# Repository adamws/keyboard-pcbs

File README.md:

# keyboard-pcbs

Collection of generated keyboard PCBs based on [via](https://github.com/the-via/keyboards.git) layouts.

:link: Visit [https://adamws.github.io/keyboard-pcbs](https://adamws.github.io/keyboard-pcbs) to view results.

> [!WARNING]
> This is a showcase/benchmark of [kicad-kbplacer](https://github.com/adamws/kicad-kbplacer) plugin.
> All of the KiCad files are automatically generated and *may* contain errors.
> These *are not* production ready PCBs.

## How to run

The procedure of generating `keyboard-pcbs` website is split into two stages
which can be repeated locally using builder docker image.

- Download all layouts from [via](https://github.com/the-via/keyboards.git)
repository and generate KiCad schematic and PCB file for each one.

  ```bash
  $ docker run --rm -v $(pwd):/work \
      ghcr.io/adamws/keyboard-pcbs-maker:latest python via_layouts_to_boards.py generate
  ```

- Collect results from first stage and create static website to be deployed

  ```bash
  $ docker run --rm -v $(pwd):/work \
      ghcr.io/adamws/keyboard-pcbs-maker:latest python via_layouts_to_boards.py collect
  ```

> [!WARNING]
> This takes long time and is resource consuming.
> It runs on schedule using [Github Actions](https://github.com/adamws/keyboard-pcbs/actions/workflows/main.yml).

To see results, go to output directory and start http server with python:

```bash
$ cd gh-pages
$ python -m http.server
Serving HTTP on 0.0.0.0 port 8000 (http://0.0.0.0:8000/) ...
```

### Run for single layout

If you want to run this for single layout file, call `kbplacer-generate.sh` directly.
For example, navigate to directory with `.json` layout and run:

```bash
$ cd src/gh60/satan
$ ls
satan.json
$ docker run --rm -v $(pwd):/work \
    ghcr.io/adamws/keyboard-pcbs-maker:latest kbplacer-generate.sh /work satan
```

Note that second argument passed to `kbplacer-generate.sh` does not contain file extension.

When container finish, current directory should contain following files:

```bash
$ ls
satan.json      satan-layout.svg  satan-schematic.svg
satan-kle.json  satan-render.svg  satan.zip
$ unzip satan.zip
Archive:  satan.zip
  inflating: satan.kicad_pro
  inflating: satan.kicad_sch
  inflating: satan.kicad_pcb
  inflating: satan.net
```

| satan-layout.svg                      |
| :-:                                   |
|  |

| satan-layout.svg                                                                                                   | satan-render.svg                                                                                                |
| :-:                                                                                                                | :-:                                                                                                             |
|                                                                         |                                                                        |
| [open in new window](https://raw.githubusercontent.com/adamws/keyboard-pcbs/master/resources/satan-schematic.svg)  | [open in new window](https://raw.githubusercontent.com/adamws/keyboard-pcbs/master/resources/satan-render.svg)  |

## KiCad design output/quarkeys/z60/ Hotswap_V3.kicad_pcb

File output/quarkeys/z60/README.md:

## quarkeys/z60/Hotswap-V2

[layout](Hotswap-V2-kle.json) - [PCB](Hotswap-V2.kicad_pcb)

{:loading="lazy"}

[Open in keyboard-layout-editor](http://www.keyboard-layout-editor.com/##@@_x:1&c=#aaaaaa;&=0,0&_c=#cccccc;&=0,1&=0,2&=0,3&=0,4&=0,5&=0,6&=0,7&=0,8&=0,9&=0,10&=0,11&=0,12&_w:2;&=0,14;&@_x:1&w:1.5;&=1,0&=1,2&=1,3&=1,4&=1,5&=1,6&=1,7&=1,8&=1,9&=1,10&=1,11&=1,12&=1,13&_w:1.5;&=1,14;&@_x:1&w:1.75;&=2,0&=2,2&=2,3&=2,4&=2,5&=2,6&=2,7&=2,8&=2,9&=2,10&=2,11&=2,12&_w:2.25;&=2,13;&@_x:1&w:2.25;&=3,1&=3,2&=3,3&=3,4&=3,5&=3,6&=3,7&=3,8&=3,9&=3,10&=3,11&_w:1.75;&=3,13&=3,14;&@_x:1&w:1.5;&=4,0&=4,2&_w:1.5;&=4,3&_w:7;&=4,7&_w:1.5;&=4,11&=4,13&_w:1.5;&=4,14)

{:loading="lazy"}

## quarkeys/z60/Solder-V2

[layout](Solder-V2-kle.json) - [PCB](Solder-V2.kicad_pcb)

{:loading="lazy"}

[Open in keyboard-layout-editor](http://www.keyboard-layout-editor.com/##@@_x:2.5&c=#777777;&=0,0&_c=#cccccc;&=0,1&=0,2&=0,3&=0,4&=0,5&=0,6&=0,7&=0,8&=0,9&=0,10&=0,11&=0,12&_c=#aaaaaa&w:2;&=0,13%0A%0A%0A0,0;&@_x:2.5&w:1.5;&=1,1&_c=#cccccc;&=1,2&=1,3&=1,4&=1,5&=1,6&=1,7&=1,8&=1,9&=1,10&=1,11&=1,12&=1,13&_w:1.5;&=1,14%0A%0A%0A1,0;&@_x:2.5&c=#aaaaaa&w:1.75;&=2,1&_c=#cccccc;&=2,2&=2,3&=2,4&=2,5&=2,6&=2,7&=2,8&=2,9&=2,10&=2,11&=2,12&_c=#777777&w:2.25;&=2,14%0A%0A%0A1,0;&@_x:2.5&c=#aaaaaa&w:2.25;&=3,0%0A%0A%0A2,0&_c=#cccccc;&=3,2&=3,3&=3,4&=3,5&=3,6&=3,7&=3,8&=3,9&=3,10&=3,11&_c=#aaaaaa&w:2.75;&=3,12%0A%0A%0A3,0;&@_x:2.5&w:1.25;&=4,0%0A%0A%0A4,0&_w:1.25;&=4,1%0A%0A%0A4,0&_w:1.25;&=4,3%0A%0A%0A4,0&_c=#cccccc&w:6.25;&=4,6%0A%0A%0A4,0&_c=#aaaaaa&w:1.25;&=4,10%0A%0A%0A4,0&_w:1.25;&=4,11%0A%0A%0A4,0&_w:1.25;&=4,12%0A%0A%0A4,0&_w:1.25;&=4,13%0A%0A%0A4,0;&@_x:18.0&y:-5&c=#cccccc;&=0,13%0A%0A%0A0,1&=0,14%0A%0A%0A0,1;&@_x:18.75&c=#777777&w:1.25&h:2&w2:1.5&h2:1&x2:-0.25;&=2,14%0A%0A%0A1,1;&@_x:17.75&c=#cccccc;&=2,13%0A%0A%0A1,1;&@_c=#aaaaaa&w:1.25;&=3,0%0A%0A%0A2,1&=3,1%0A%0A%0A2,1&_x:15.5&w:1.75;&=3,12%0A%0A%0A3,1&=3,13%0A%0A%0A3,1;&@_x:2.5&y:1.5&w:1.5;&=4,0%0A%0A%0A4,1&=4,1%0A%0A%0A4,1&_w:1.5;&=4,3%0A%0A%0A4,1&_c=#cccccc&w:7;&=4,6%0A%0A%0A4,1&_c=#aaaaaa&w:1.5;&=4,11%0A%0A%0A4,1&=4,12%0A%0A%0A4,1&_w:1.5;&=4,13%0A%0A%0A4,1;&@_x:2.5&w:1.5&d:true;&=4,0%0A%0A%0A4,2&=4,1%0A%0A%0A4,2&_w:1.5;&=4,3%0A%0A%0A4,2&_c=#cccccc&w:7;&=4,6%0A%0A%0A4,2&_c=#aaaaaa&w:1.5;&=4,11%0A%0A%0A4,2&=4,12%0A%0A%0A4,2&_w:1.5&d:true;&=4,13%0A%0A%0A4,2;&@_x:2.5&w:1.5;&=4,0%0A%0A%0A4,3&_d:true;&=4,1%0A%0A%0A4,3&_w:1.5;&=4,3%0A%0A%0A4,3&_c=#cccccc&w:7;&=4,6%0A%0A%0A4,3&_c=#aaaaaa&w:1.5;&=4,11%0A%0A%0A4,3&_d:true;&=4,12%0A%0A%0A4,3&_w:1.5;&=4,13%0A%0A%0A4,3)

{:loading="lazy"}

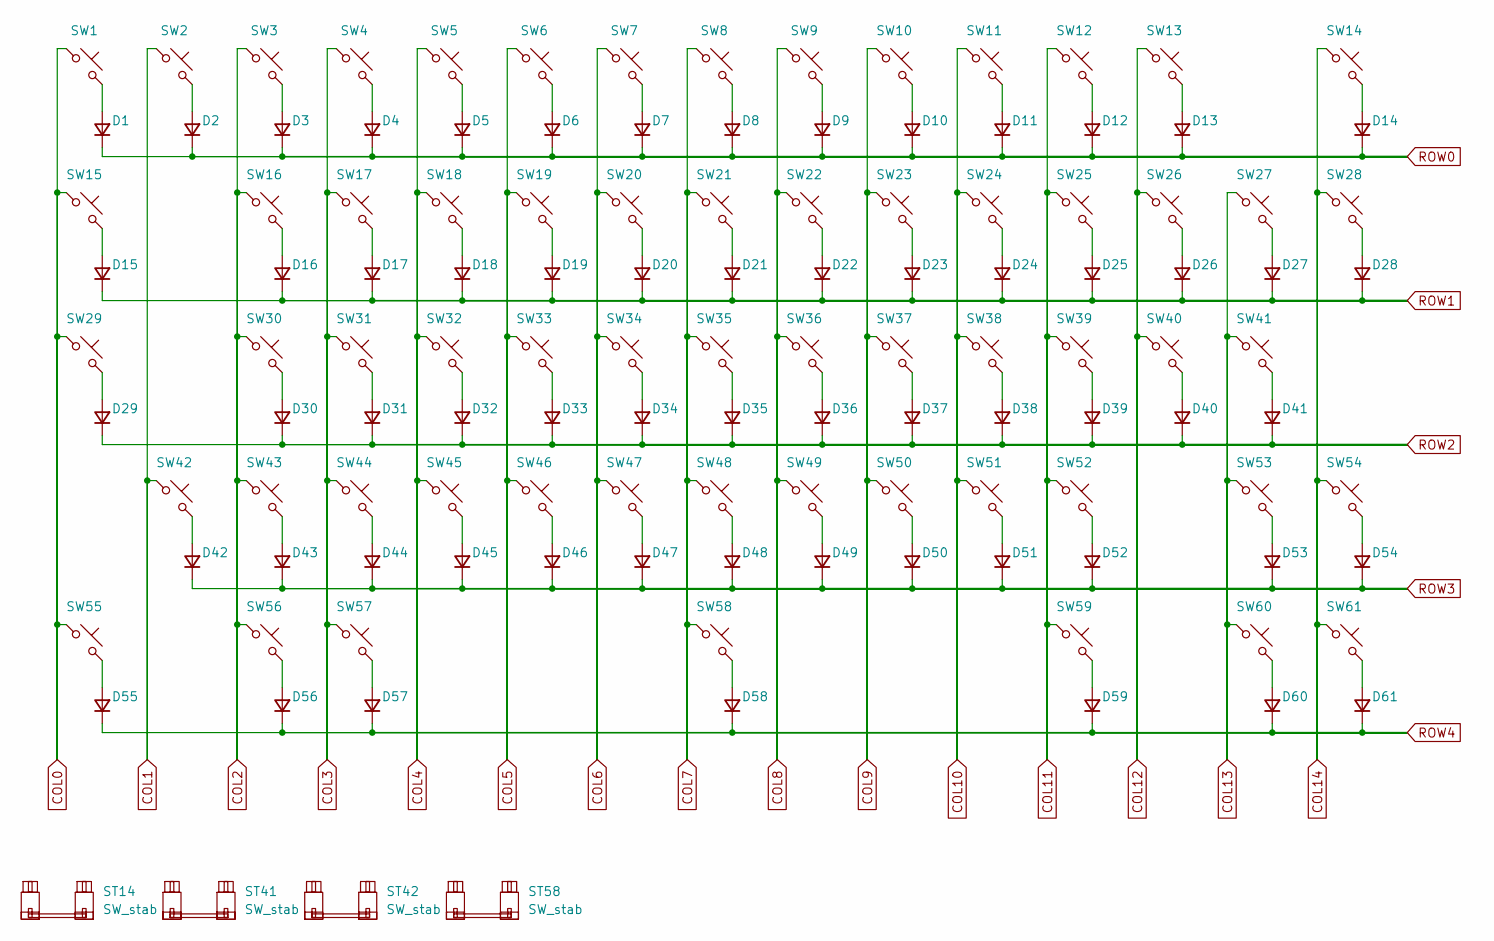
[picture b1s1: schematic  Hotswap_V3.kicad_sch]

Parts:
D1, D2, D3, D4, D5, D6, D7, D8, D9, D10, D11, D12, D13, D14, D15, D16, D17, D18, D19, D20, D21, D22, D23, D24, D25, D26, D27, D28, D29, D30, D31, D32, D33, D34, D35, D36, D37, D38, D39, D40, D41, D42, D43, D44, D45, D46, D47, D48, D49, D50, D51, D52, D53, D54, D55, D56, D57, D58, D59, D60, D61: D; D_SOD-123F
ST14, ST41, ST42: SW_stab; Stabilizer_Cherry_MX_2.00u
ST58: SW_stab; Stabilizer_Cherry_MX_7.00u
SW1, SW2, SW3, SW4, SW5, SW6, SW7, SW8, SW9, SW10, SW11, SW12, SW13, SW16, SW17, SW18, SW19, SW20, SW21, SW22, SW23, SW24, SW25, SW26, SW27, SW30, SW31, SW32, SW33, SW34, SW35, SW36, SW37, SW38, SW39, SW40, SW43, SW44, SW45, SW46, SW47, SW48, SW49, SW50, SW51, SW52, SW54, SW56, SW60: SW_Push; SW_Cherry_MX_PCB_1.00u
SW14: SW_Push; SW_Cherry_MX_PCB_2.00u
SW15, SW28, SW55, SW57, SW59, SW61: SW_Push; SW_Cherry_MX_PCB_1.50u
SW29, SW53: SW_Push; SW_Cherry_MX_PCB_1.75u
SW41, SW42: SW_Push; SW_Cherry_MX_PCB_2.25u
SW58: SW_Push; SW_Cherry_MX_PCB_7.00u

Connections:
COL0: SW1.1, SW15.1, SW29.1, SW55.1
COL1: SW2.1, SW42.1
COL2: SW3.1, SW16.1, SW30.1, SW43.1, SW56.1
COL3: SW4.1, SW17.1, SW31.1, SW44.1, SW57.1
COL4: SW5.1, SW18.1, SW32.1, SW45.1
COL5: SW6.1, SW19.1, SW33.1, SW46.1
COL6: SW7.1, SW20.1, SW34.1, SW47.1
COL7: SW8.1, SW21.1, SW35.1, SW48.1, SW58.1
COL8: SW9.1, SW22.1, SW36.1, SW49.1
COL9: SW10.1, SW23.1, SW37.1, SW50.1
COL10: SW11.1, SW24.1, SW38.1, SW51.1
COL11: SW12.1, SW25.1, SW39.1, SW52.1, SW59.1
COL12: SW13.1, SW26.1, SW40.1
COL13: SW27.1, SW41.1, SW53.1, SW60.1
COL14: SW14.1, SW28.1, SW54.1, SW61.1
unnamed: D1.2 (A), SW1.2
unnamed: D2.2 (A), SW2.2
unnamed: D3.2 (A), SW3.2
unnamed: D4.2 (A), SW4.2
unnamed: D5.2 (A), SW5.2
unnamed: D6.2 (A), SW6.2
unnamed: D7.2 (A), SW7.2
unnamed: D8.2 (A), SW8.2
unnamed: D9.2 (A), SW9.2
unnamed: D10.2 (A), SW10.2
unnamed: D11.2 (A), SW11.2
unnamed: D12.2 (A), SW12.2
unnamed: D13.2 (A), SW13.2
unnamed: D14.2 (A), SW14.2
unnamed: D15.2 (A), SW15.2
unnamed: D16.2 (A), SW16.2
unnamed: D17.2 (A), SW17.2
unnamed: D18.2 (A), SW18.2
unnamed: D19.2 (A), SW19.2
unnamed: D20.2 (A), SW20.2
unnamed: D21.2 (A), SW21.2
unnamed: D22.2 (A), SW22.2
unnamed: D23.2 (A), SW23.2
unnamed: D24.2 (A), SW24.2
unnamed: D25.2 (A), SW25.2
unnamed: D26.2 (A), SW26.2
unnamed: D27.2 (A), SW27.2
unnamed: D28.2 (A), SW28.2
unnamed: D29.2 (A), SW29.2
unnamed: D30.2 (A), SW30.2
unnamed: D31.2 (A), SW31.2
unnamed: D32.2 (A), SW32.2
unnamed: D33.2 (A), SW33.2
unnamed: D34.2 (A), SW34.2
unnamed: D35.2 (A), SW35.2
unnamed: D36.2 (A), SW36.2
unnamed: D37.2 (A), SW37.2
unnamed: D38.2 (A), SW38.2
unnamed: D39.2 (A), SW39.2
unnamed: D40.2 (A), SW40.2
unnamed: D41.2 (A), SW41.2
unnamed: D42.2 (A), SW42.2
unnamed: D43.2 (A), SW43.2
unnamed: D44.2 (A), SW44.2
unnamed: D45.2 (A), SW45.2
unnamed: D46.2 (A), SW46.2
unnamed: D47.2 (A), SW47.2
unnamed: D48.2 (A), SW48.2
unnamed: D49.2 (A), SW49.2
unnamed: D50.2 (A), SW50.2
unnamed: D51.2 (A), SW51.2
unnamed: D52.2 (A), SW52.2
unnamed: D53.2 (A), SW53.2
unnamed: D54.2 (A), SW54.2
unnamed: D55.2 (A), SW55.2
unnamed: D56.2 (A), SW56.2
unnamed: D57.2 (A), SW57.2
unnamed: D58.2 (A), SW58.2
unnamed: D59.2 (A), SW59.2
unnamed: D60.2 (A), SW60.2
unnamed: D61.2 (A), SW61.2
ROW0: D1.1 (K), D2.1 (K), D3.1 (K), D4.1 (K), D5.1 (K), D6.1 (K), D7.1 (K), D8.1 (K), D9.1 (K), D10.1 (K), D11.1 (K), D12.1 (K), D13.1 (K), D14.1 (K)
ROW1: D15.1 (K), D16.1 (K), D17.1 (K), D18.1 (K), D19.1 (K), D20.1 (K), D21.1 (K), D22.1 (K), D23.1 (K), D24.1 (K), D25.1 (K), D26.1 (K), D27.1 (K), D28.1 (K)
ROW2: D29.1 (K), D30.1 (K), D31.1 (K), D32.1 (K), D33.1 (K), D34.1 (K), D35.1 (K), D36.1 (K), D37.1 (K), D38.1 (K), D39.1 (K), D40.1 (K), D41.1 (K)
ROW3: D42.1 (K), D43.1 (K), D44.1 (K), D45.1 (K), D46.1 (K), D47.1 (K), D48.1 (K), D49.1 (K), D50.1 (K), D51.1 (K), D52.1 (K), D53.1 (K), D54.1 (K)
ROW4: D55.1 (K), D56.1 (K), D57.1 (K), D58.1 (K), D59.1 (K), D60.1 (K), D61.1 (K)

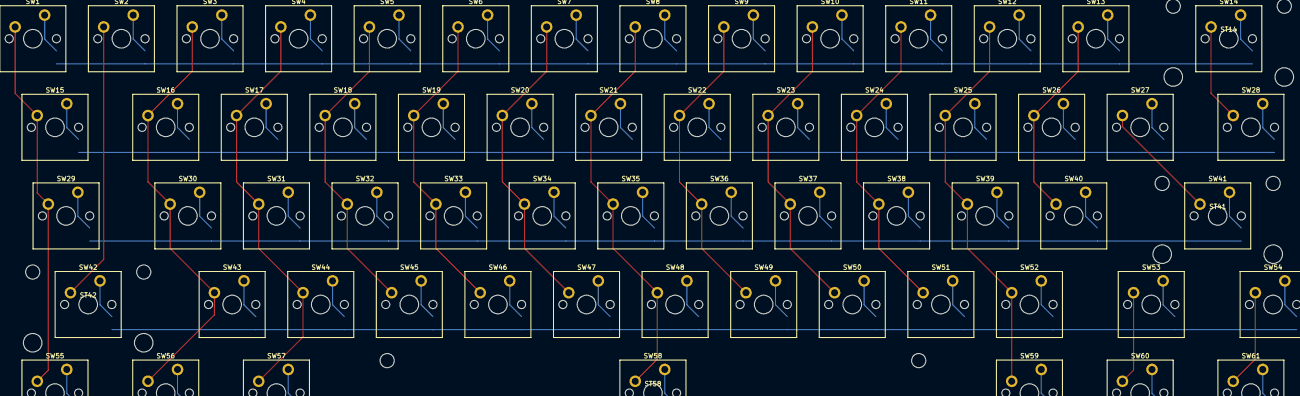
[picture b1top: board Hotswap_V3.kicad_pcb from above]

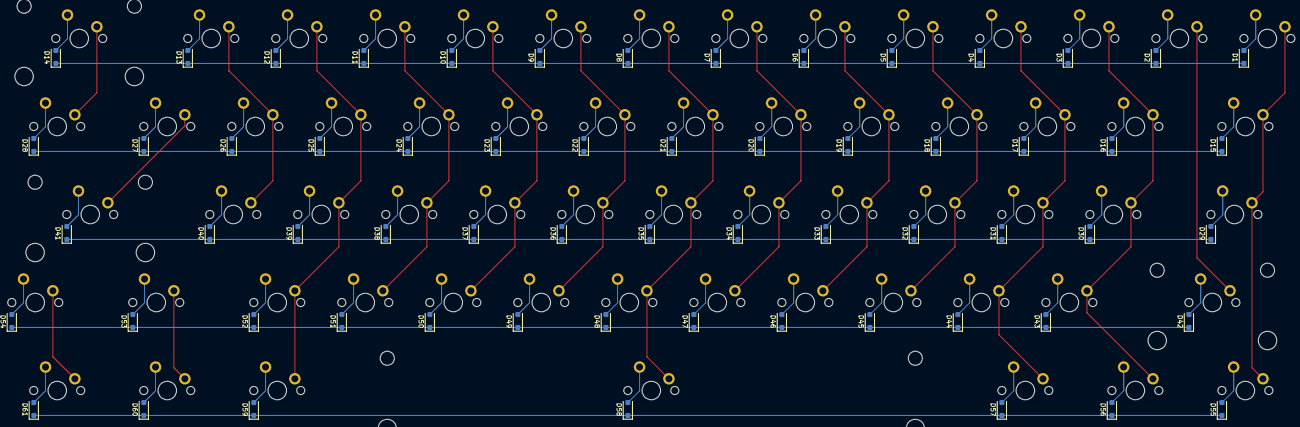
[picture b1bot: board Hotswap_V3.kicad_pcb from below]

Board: 2 copper layers, 126 parts (61 on the bottom side), 81 nets.

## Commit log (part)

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2023-10-04 Improve rendering of ISO enters for layout images
2023-10-05 Add support for keycap colors
2023-10-05 Add GitHub actions workflow
2023-12-31 Add svg optimization stage
    This reduces result directory from ~600M to ~350M
2023-12-31 Add page deploying job
2023-12-31 Introduce multiprocess operation
    Generate files inside process pool for improved performance, move readme
    file generation outside layout processing loop (it is much faster in
    comparison and it is easier that way when we want to preserve order in
    markdown files)
2023-12-31 Fix automatic page deployment
2023-12-31 Run on schedule only when via revision has changed
2024-01-01 Collect error messages and display summary
2024-01-01 Include nested vendor directories
    A lot of keyboard were missing because many use nested directories which
    were not included in glob pattern.
2024-01-01 Introduce lazy loading
2024-01-04 deploy: ea8d1de490433559f5b46d86ef454cbe0145aab8
2024-01-15 Add label for rotary encoders
2024-01-17 Add option for splitting processing into multiple parts
2024-01-17 Fix rendering for some illegal colors in layouts
2024-01-17 Fix pcb file generation for layouts with decal keys
2024-01-17 Fix rendering when top left label missing
2024-01-17 Add anchor links
2024-01-17 Build html website from scratch, stop using markdown
    Changed from markdown files to building html from template. This allows
    for easy interface upgrades without learning static-site builder
    frameworks. Added slider for filtering layouts by number of keys.
2024-01-18 Add keyboard type checkboxes
2024-01-18 Add scroll to top button
2024-01-20 Fix improper tagging of some layouts
    Fixes #1
2024-01-20 Switch to develop version of kbplacer
    This solves some layout parsing issues
2024-01-20 Minor cleanup
2024-01-21 Update dependencies
2024-01-24 Fix KLE links for layouts which contain `_` in metadata field
    Fixes #2
2024-01-26 Update checkout action
2024-02-04 Remove no longer necessary workaround
2024-02-19 Update usage according to latest `kbplacer` API changes
2024-02-19 Change diode footprint and move its position slightly
2024-02-22 Switch back to master
2024-03-28 deploy: 82dd3dc8981f606942d1448f43376f54b0626632
2024-05-04 Dockerize and run with schematic generation tool
2024-05-04 [ImgBot] Optimize images
    *Total -- 1,000.59kb -> 881.46kb (11.91%)
    /resources/satan-schematic.svg -- 541.97kb -> 466.47kb (13.93%)
    /resources/satan-render.svg -- 418.19kb -> 376.43kb (9.99%)
    /resources/satan-layout.svg -- 40.42kb -> 38.55kb (4.63%)
2024-05-05 Fix image tag in example commands
2024-05-05 Pin to specific revision of kbplacer
2024-06-08 deploy: af22b419cc9f7746588a1ab7732df0512bc7b4d4
2024-08-01 deploy: 1b7a9ae1f719cbe98fad0c3bb7993e0dac377252
2024-09-06 Detect layout duplications
2024-09-06 Upload final build result
2024-09-06 Add link to VIA repository file
2024-09-06 Order keyboards alphabetically ignoring case
2024-09-06 Remove partial results
2024-09-06 Add GitHub button
2024-09-12 Update base image
2024-09-12 Get summary on unconnected items
    This can be used to compare kbplacer router quality
2024-09-21 Update to https
    Adjust url after changes in [1]
    [1] https://github.com/ijprest/keyboard-layout-editor/commit/580b916084e69e600b2144b0217c8b1d9710daa0
2024-09-28 Update kbplacer version
2024-10-07 Enable umami analytics
2024-10-15 deploy: f68e2858eb01dfc5510a7e2f637aaa9293171077
2025-04-11 Switch to v3 via layouts
2025-04-11 Update kbplacer and base docker image
2025-04-12 Switch to latests develop kbplacer revision
2025-04-16 deploy: 61fa8ee579ef54773764a4895cea593b67b593df
2025-08-10 Add some basic minimization before publishing
2025-08-22 Use newer kbplacer version with fixed layout svg generation
2025-08-24 deploy: a31ee221874524206a3c26024da249b64f1269b4
2025-10-02 Update kbplacer revision
2025-10-02 Switch to new layout editor website
2026-05-07 Add filtering by encoder presence
2026-05-07 Create json with all keyboards list
2026-05-07 Update actions versions
2026-06-03 Add support for encoder footprints
2026-06-04 Pin kbplacer to specific revision
2026-06-05 Use kbplacer release version
2026-06-05 Update action version
2026-06-05 Remove middle label from encoders
2026-06-17 Enable placing stabilizers and capture kbplacer output to log
2026-06-18 Update satan example output
2026-06-23 Add full log path to error message
